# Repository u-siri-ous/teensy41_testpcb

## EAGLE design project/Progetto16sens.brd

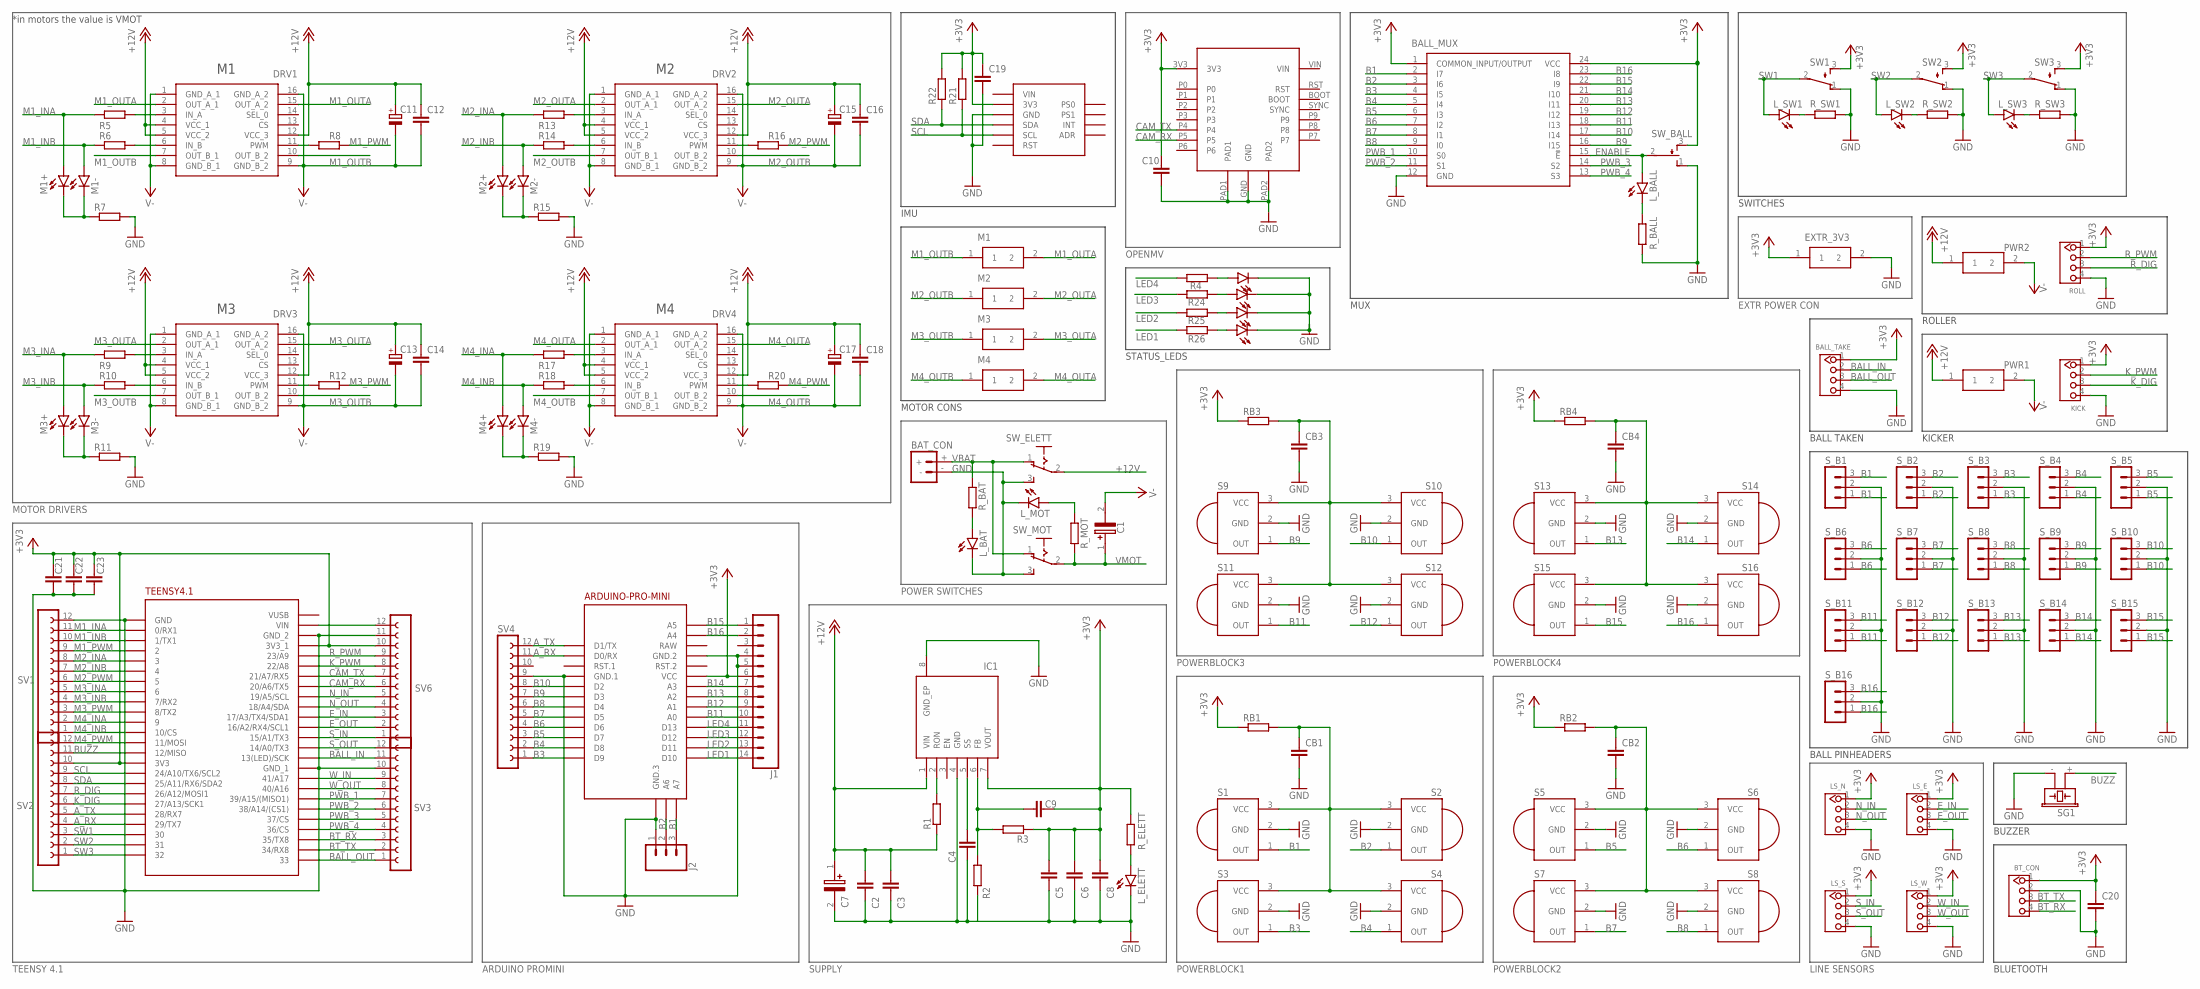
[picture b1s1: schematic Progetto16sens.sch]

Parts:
BALL_MUX: CD74HC4067M; SOIC127P1030X265-24N
BALL_TAKE: 4P-2.0; HW4-2.0
BAT_CON: BATTERY_CONN_DEANS; DEANS
BT_CON: 4P-2.0; HW4-2.0
C1, C7: EEV-FK1C152Q; FKV(H13)
C2, C3, C8: 100n; C0805
C4, C9: 22n; C0805
C5, C6, C10: 100u; C1206
C11, C13, C15, C17: CPOL-EUE; PANASONIC_E
C12, C14, C16, C18, C22, C23: C-EUC0805; C0805
C19, C20: 1u; C0805
C21: C-EUC1206; C1206
CB1, CB2, CB3, CB4: C-EUC0805; C0805
DRV1, DRV2, DRV3, DRV4: VNH7070ASTR; SOIC127P600X175-16N
EXTR_3V3: 43650-0201; 43650-0200
IC1: LMZ14202TZE-ADJ_NOPB; NDW0007A
J1: CONN_14; 1X14
J2: 455-1750-1-ND; 1X03
KICK: TWIG_2.0; 2.0_1X4
LED1, LED2, LED3, LED4: LEDCHIPLED_1206; CHIPLED_1206
LS_E: 4P-2.0; HW4-2.0
LS_N: 4P-2.0; HW4-2.0
LS_S: 4P-2.0; HW4-2.0
LS_W: 4P-2.0; HW4-2.0
L_BALL: LEDCHIPLED_1206; CHIPLED_1206
L_BAT: LEDCHIPLED_1206; CHIPLED_1206
L_ELETT: LEDCHIPLED_1206; CHIPLED_1206
L_MOT: LEDCHIPLED_1206; CHIPLED_1206
L_SW1, L_SW2, L_SW3: LEDCHIPLED_1206; CHIPLED_1206
M1, M2, M3, M4: 43650-0201; 43650-0200
M1+, M1-, M2+, M2-, M3+, M3-, M4+, M4-: LEDCHIPLED_1206; CHIPLED_1206
M5: ARDUINO-PRO-MINI; ARDUINO-PRO-MINI#NP
PWR1, PWR2: 43650-0201; 43650-0200
R1: 61,9k; M0805
R2: 1,07k; M0805
R3: 3,32k; M0805
R4, R24, R25, R26: R-EU_R0805; R0805
R5, R6, R7, R8, R9, R10, R11, R12, R13, R14, R15, R16, R17, R18, R19, R20: R-EU_M0805; M0805
R21, R22: 10k; M0805
RB1, RB2, RB3, RB4: R-EU_M0805; M0805
ROLL: TWIG_2.0; 2.0_1X4
R_BALL: R-EU_M0805; M0805
R_BAT: R-EU_M0805; M0805
R_ELETT: R-EU_M0805; M0805
R_MOT: R-EU_M0805; M0805
R_SW1, R_SW2, R_SW3: R-EU_M0805; M0805
S1, S2, S3, S4, S5, S6, S7, S8, S9, S10, S11, S12, S13, S14, S15, S16: PNA460XM
SG1: F/CM12P
SV1, SV2, SV3, SV4, SV6: FE12-1; FE12
SW1, SW2, SW3: TL32PO; TL3XPO
SW_BALL: TL38PO; TL3XPO
SW_ELETT: 255SB
SW_MOT: 255SB
S_B1, S_B2, S_B3, S_B4, S_B5, S_B6, S_B7, S_B8, S_B9, S_B10, S_B11, S_B12, S_B13, S_B14, S_B15, S_B16: MA03-1
U$1: TEENSY41_EDIT
U$2: OPENMV_H7
U$3: BNO055_BNO055

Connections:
+3V3: BALL_MUX.1 (COMMON_INPUT/OUTPUT), BALL_MUX.24 (VCC), BALL_TAKE.1, BT_CON.1, C5.1, C6.1, C8.1, C9.2, C10.1, C19.1, C20.1, C21.1, C22.1, C23.1, EXTR_3V3.1, IC1.7 (VOUT), J1.6, KICK.1, LS_E.1, LS_N.1, LS_S.1, LS_W.1, M5.J6.4 (VCC), R3.1, R21.2, R22.2, RB1.1, RB2.1, RB3.1, RB4.1, ROLL.1, R_ELETT.2, SV2.10, SV6.10, SW1.3 (S), SW2.3 (S), SW3.3 (S), SW_BALL.3 (S), U$1.3V3, U$1.3V3_1, U$2.3V3, U$3.3V3
+12V: C2.1, C3.1, C7.1 (+), IC1.1 (VIN), R1.1, SW_ELETT.2
A_RX: M5.J7.11 (D0/RX), SV2.4, SV4.11, U$1.29/TX7
A_TX: M5.J7.12 (D1/TX), SV2.5, SV4.12, U$1.28/RX7
B1: BALL_MUX.2 (I7), J2.3, M5.J3.3 (A7), S1.1 (OUT), S_B1.1, S_B1.3
B2: BALL_MUX.3 (I6), J2.2, M5.J3.2 (A6), S2.1 (OUT), S_B2.1, S_B2.3
B3: BALL_MUX.4 (I5), M5.J7.1 (D9), S3.1 (OUT), SV4.1, S_B3.1, S_B3.3
B4: BALL_MUX.5 (I4), M5.J7.2 (D8), S4.1 (OUT), SV4.2, S_B4.1, S_B4.3
B5: BALL_MUX.6 (I3), M5.J7.3 (D7), S5.1 (OUT), SV4.3, S_B5.1, S_B5.3
B6: BALL_MUX.7 (I2), M5.J7.4 (D6), S6.1 (OUT), SV4.4, S_B6.1, S_B6.3
B7: BALL_MUX.8 (I1), M5.J7.5 (D5), S7.1 (OUT), SV4.5, S_B7.1, S_B7.3
B8: BALL_MUX.9 (I0), M5.J7.6 (D4), S8.1 (OUT), SV4.6, S_B8.1, S_B8.3
B9: BALL_MUX.16 (I15), M5.J7.7 (D3), S9.1 (OUT), SV4.7, S_B9.1, S_B9.3
B10: BALL_MUX.17 (I14), M5.J7.8 (D2), S10.1 (OUT), SV4.8, S_B10.1, S_B10.3
B11: BALL_MUX.18 (I13), J1.10, M5.J6.8 (A0), S11.1 (OUT), S_B11.1, S_B11.3
B12: BALL_MUX.19 (I12), J1.9, M5.J6.7 (A1), S12.1 (OUT), S_B12.1, S_B12.3
B13: BALL_MUX.20 (I11), J1.8, M5.J6.6 (A2), S13.1 (OUT), S_B13.1, S_B13.3
B14: BALL_MUX.21 (I10), J1.7, M5.J6.5 (A3), S14.1 (OUT), S_B14.1, S_B14.3
B15: BALL_MUX.22 (I9), J1.1, M5.J2.2 (A5), S15.1 (OUT), S_B15.1, S_B15.3
B16: BALL_MUX.23 (I8), J1.2, M5.J2.1 (A4), S16.1 (OUT), S_B16.1, S_B16.3
BALL_IN: BALL_TAKE.2, SV3.11, U$1.13(LED)/SCK
BALL_OUT: BALL_TAKE.3, SV3.1, U$1.33
BT_RX: BT_CON.4, SV3.3, U$1.35/TX8
BT_TX: BT_CON.3, SV3.2, U$1.34/RX8
BUZZ: SG1.+ (1), SV2.11, U$1.12/MISO
CAM_RX: SV6.6, U$1.20/A6/TX5, U$2.P5
CAM_TX: SV6.7, U$1.21/A7/RX5, U$2.P4
ENABLE: BALL_MUX.15 (!E), L_BALL.A, SW_BALL.2
E_IN: LS_E.2, SV6.3, U$1.17/A3/TX4/SDA1
E_OUT: LS_E.3, SV6.2, U$1.16/A2/RX4/SCL1
GND: BALL_MUX.12 (GND), BALL_TAKE.4, BAT_CON.-, BT_CON.2, C2.2, C3.2, C4.2, C5.2, C6.2, C7.2 (-), C8.2, C10.2, C19.2, C20.2, C21.2, C22.2, C23.2, CB1.2, CB2.2, CB3.2, CB4.2, EXTR_3V3.2, IC1.4 (GND), IC1.8 (GND_EP), J1.4, J1.5, J2.1, KICK.4, LED1.C, LED2.C, LED3.C, LED4.C, LS_E.4, LS_N.4, LS_S.4, LS_W.4, L_BAT.C, L_ELETT.C, L_MOT.C, M5.J3.1 (GND.3), M5.J6.2 (GND.2), M5.J7.9 (GND.1), R2.1, R7.2, R11.2, R15.2, R19.2, ROLL.4, R_BALL.1, R_SW1.1, R_SW2.1, R_SW3.1, S1.2 (GND), S2.2 (GND), S3.2 (GND), S4.2 (GND), S5.2 (GND), S6.2 (GND), S7.2 (GND), S8.2 (GND), S9.2 (GND), S10.2 (GND), S11.2 (GND), S12.2 (GND), S13.2 (GND), S14.2 (GND), S15.2 (GND), S16.2 (GND), SG1.- (2), SV1.12, SV3.10, SV4.9, SV6.11, SW1.1 (O), SW2.1 (O), SW3.1 (O), SW_BALL.1 (O), SW_ELETT.3 (S), SW_MOT.3 (S), S_B1.2, S_B2.2, S_B3.2, S_B4.2, S_B5.2, S_B6.2, S_B7.2, S_B8.2, S_B9.2, S_B10.2, S_B11.2, S_B12.2, S_B13.2, S_B14.2, S_B15.2, S_B16.2, U$1.GND, U$1.GND_1, U$1.GND_2, U$2.GND, U$2.PAD1, U$2.PAD2, U$3.GND
K_DIG: KICK.3, SV2.6, U$1.27/A13/SCK1
K_PWM: KICK.2, SV6.8, U$1.22/A8
LED1: J1.14, M5.J6.12 (D10), R26.1
LED2: J1.13, M5.J6.11 (D11), R25.1
LED3: J1.12, M5.J6.10 (D12), R24.1
LED4: J1.11, M5.J6.9 (D13), R4.1
M1_INA: M1+.A, R5.1, SV1.11, U$1.0/RX1
M1_INB: M1-.A, R6.1, SV1.10, U$1.1/TX1
M1_OUTA: DRV1.2 (OUT_A_1), DRV1.15 (OUT_A_2), M1.2
M1_OUTB: DRV1.7 (OUT_B_1), DRV1.10 (OUT_B_2), M1.1
M1_PWM: R8.2, SV1.9, U$1.2
M2_INA: M2+.A, R13.1, SV1.8, U$1.3
M2_INB: M2-.A, R14.1, SV1.7, U$1.4
M2_OUTA: DRV2.2 (OUT_A_1), DRV2.15 (OUT_A_2), M2.2
M2_OUTB: DRV2.7 (OUT_B_1), DRV2.10 (OUT_B_2), M2.1
M2_PWM: R16.2, SV1.6, U$1.5
M3_INA: M3+.A, R9.1, SV1.5, U$1.6
M3_INB: M3-.A, R10.1, SV1.4, U$1.7/RX2
M3_OUTA: DRV3.2 (OUT_A_1), DRV3.15 (OUT_A_2), M3.2
M3_OUTB: DRV3.7 (OUT_B_1), DRV3.10 (OUT_B_2), M3.1
M3_PWM: R12.2, SV1.3, U$1.8/TX2
M4_INA: M4+.A, R17.1, SV1.2, U$1.9
M4_INB: M4-.A, R18.1, SV1.1, U$1.10/CS
M4_OUTA: DRV4.2 (OUT_A_1), DRV4.15 (OUT_A_2), M4.2
M4_OUTB: DRV4.7 (OUT_B_1), DRV4.10 (OUT_B_2), M4.1
M4_PWM: R20.2, SV2.12, U$1.11/MOSI
unnamed: L_SW2.C, R_SW2.2
unnamed: L_SW1.C, R_SW1.2
unnamed: L_SW3.C, R_SW3.2
unnamed: LED4.A, R4.2
unnamed: C4.1, IC1.5 (SS)
unnamed: L_BAT.A, R_BAT.2
unnamed: L_BALL.C, R_BALL.2
unnamed: L_MOT.A, R_MOT.1
unnamed: C9.1, IC1.6 (FB), R2.2, R3.2
unnamed: IC1.2 (RON), R1.2
unnamed: L_ELETT.A, R_ELETT.1
unnamed: LED2.A, R25.2
unnamed: LED3.A, R24.2
unnamed: LED1.A, R26.2
unnamed: M1+.C, M1-.C, R7.1
unnamed: DRV1.3 (IN_A), R5.2
unnamed: DRV1.6 (IN_B), R6.2
unnamed: DRV1.11 (PWM), R8.1
unnamed: DRV3.3 (IN_A), R9.2
unnamed: DRV3.6 (IN_B), R10.2
unnamed: M3+.C, M3-.C, R11.1
unnamed: DRV3.11 (PWM), R12.1
unnamed: DRV2.3 (IN_A), R13.2
unnamed: DRV2.6 (IN_B), R14.2
unnamed: M2+.C, M2-.C, R15.1
unnamed: DRV2.11 (PWM), R16.1
unnamed: DRV4.3 (IN_A), R17.2
unnamed: DRV4.6 (IN_B), R18.2
unnamed: M4+.C, M4-.C, R19.1
unnamed: DRV4.11 (PWM), R20.1
unnamed: SV6.12, U$1.VIN
N_IN: LS_N.2, SV6.5, U$1.19/A5/SCL
N_OUT: LS_N.3, SV6.4, U$1.18/A4/SDA
PWB_1: BALL_MUX.10 (S0), SV3.7, U$1.39/A15/(MISO1)
PWB_2: BALL_MUX.11 (S1), SV3.6, U$1.38/A14/(CS1)
PWB_3: BALL_MUX.14 (S2), SV3.5, U$1.37/CS
PWB_4: BALL_MUX.13 (S3), SV3.4, U$1.36/CS
PWR_B1: CB1.1, RB1.2, S1.3 (VCC), S2.3 (VCC), S3.3 (VCC), S4.3 (VCC)
PWR_B2: CB2.1, RB2.2, S5.3 (VCC), S6.3 (VCC), S7.3 (VCC), S8.3 (VCC)
PWR_B3: CB3.1, RB3.2, S9.3 (VCC), S10.3 (VCC), S11.3 (VCC), S12.3 (VCC)
PWR_B4: CB4.1, RB4.2, S13.3 (VCC), S14.3 (VCC), S15.3 (VCC), S16.3 (VCC)
RAW: M5.J6.1 (RAW)
R_DIG: ROLL.3, SV2.7, U$1.26/A12/MOSI1
R_PWM: ROLL.2, SV6.9, U$1.23/A9
SCL: R21.1, SV2.9, U$1.24/A10/TX6/SCL2, U$3.SCL
SDA: R22.1, SV2.8, U$1.25/A11/RX6/SDA2, U$3.SDA
SW1: L_SW1.A, SV2.3, SW1.2, U$1.30
SW2: L_SW2.A, SV2.2, SW2.2, U$1.31
SW3: L_SW3.A, SV2.1, SW3.2, U$1.32
S_IN: LS_S.2, SV6.1, U$1.15/A1/RX3 (15/A1/TX3)
S_OUT: LS_S.3, SV3.12, U$1.14/A0/TX3
V-: C1.2 (-), C11.-, C12.2, C13.-, C14.2, C15.-, C16.2, C17.-, C18.2, DRV1.1 (GND_A_1), DRV1.8 (GND_B_1), DRV1.9 (GND_B_2), DRV1.16 (GND_A_2), DRV2.1 (GND_A_1), DRV2.8 (GND_B_1), DRV2.9 (GND_B_2), DRV2.16 (GND_A_2), DRV3.1 (GND_A_1), DRV3.8 (GND_B_1), DRV3.9 (GND_B_2), DRV3.16 (GND_A_2), DRV4.1 (GND_A_1), DRV4.8 (GND_B_1), DRV4.9 (GND_B_2), DRV4.16 (GND_A_2), PWR1.2, PWR2.2
VBAT: BAT_CON.+, R_BAT.1, SW_ELETT.1 (O), SW_MOT.1 (O)
VMOT: C1.1 (+), C11.+, C12.1, C13.+, C14.1, C15.+, C16.1, C17.+, C18.1, DRV1.4 (VCC_1), DRV1.5 (VCC_2), DRV1.12 (VCC_3), DRV2.4 (VCC_1), DRV2.5 (VCC_2), DRV2.12 (VCC_3), DRV3.4 (VCC_1), DRV3.5 (VCC_2), DRV3.12 (VCC_3), DRV4.4 (VCC_1), DRV4.5 (VCC_2), DRV4.12 (VCC_3), PWR1.1, PWR2.1, R_MOT.2, SW_MOT.2
W_IN: LS_W.2, SV3.9, U$1.41/A17
W_OUT: LS_W.3, SV3.8, U$1.40/A16

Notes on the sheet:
TEENSY 4.1
ARDUINO PROMINI
POWERBLOCK1
POWERBLOCK2
POWERBLOCK3
POWERBLOCK4
SUPPLY
MOTOR DRIVERS
EXTR POWER CON
LINE SENSORS
OPENMV
POWER SWITCHES
MOTOR CONS
IMU
BLUETOOTH
BALL PINHEADERS
MUX
TEENSY4.1
BUZZER
SWITCHES
STATUS_LEDS
ROLLER
KICKER
*in motors the value is VMOT
BALL TAKEN

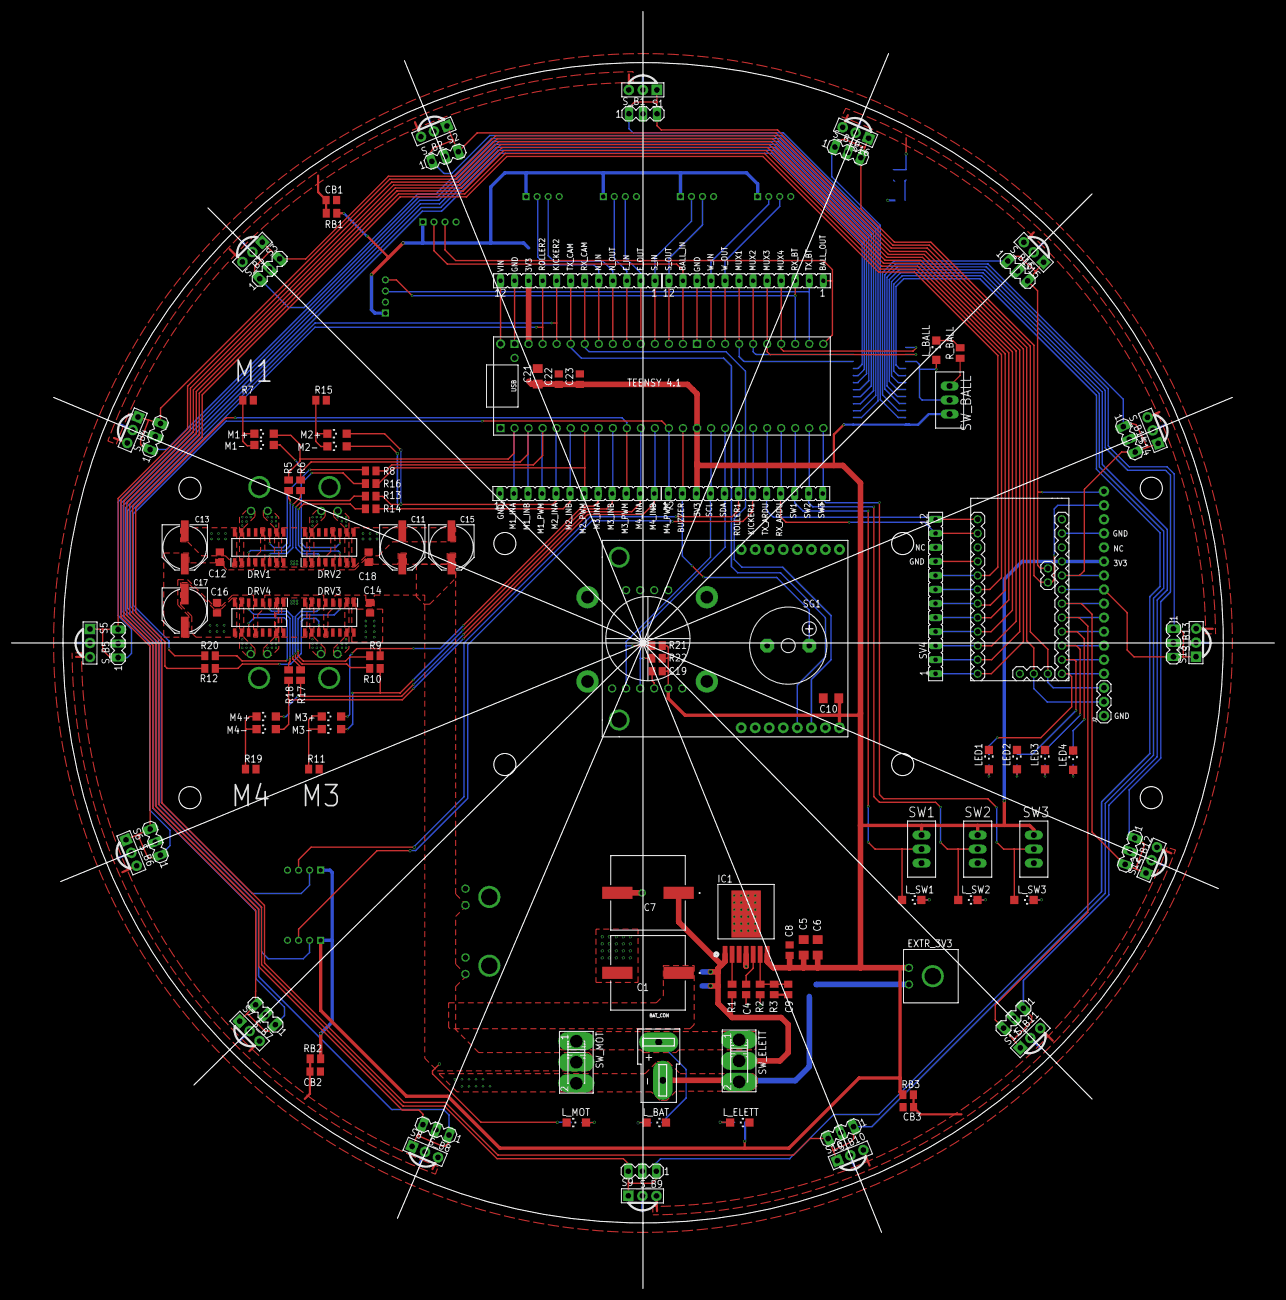
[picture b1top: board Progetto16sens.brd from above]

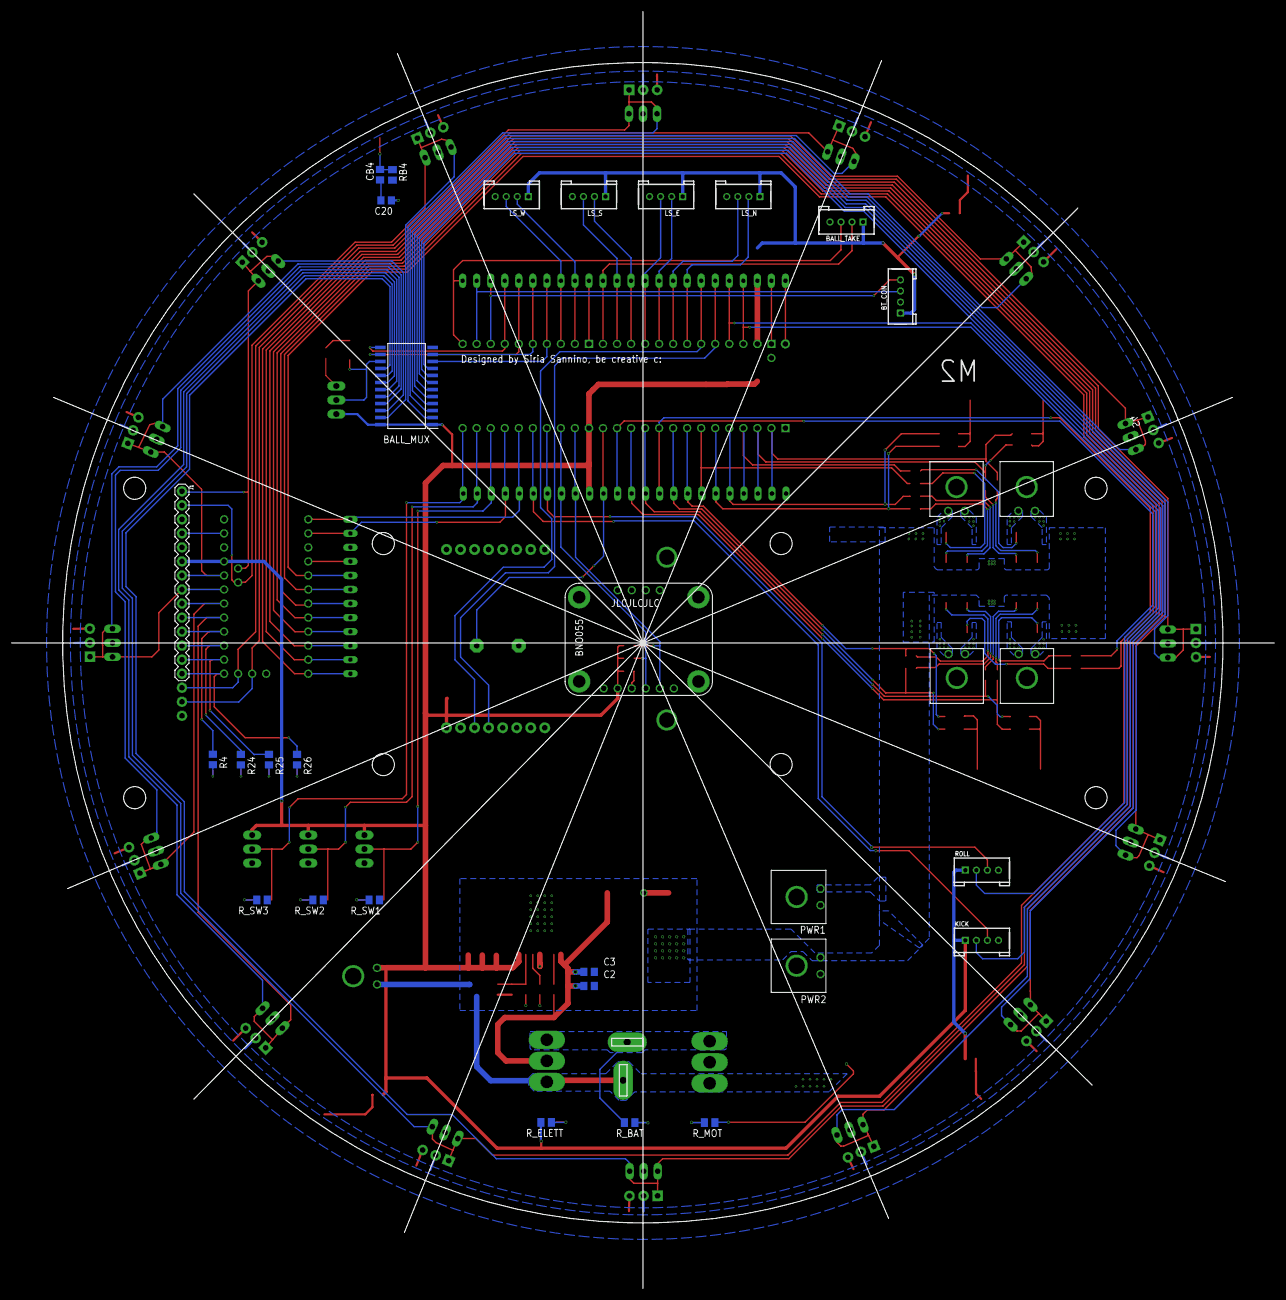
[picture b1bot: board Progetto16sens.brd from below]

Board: 2 copper layers, 210.0 x 210.0 mm, 154 parts (32 on the bottom side), 112 nets.

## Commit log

2021-03-23 first commit, yay! c:
2021-03-23 added camera and motor cons
2021-03-24 integrated new libs, added a todo and line sensors
2021-03-24 added motor drivers, found a problem in brd creation tho :c
2021-03-27 created the array of ball sensors, now to understand how to rotate them right, implementing a custom made IMU lbr
2021-03-27 started placing components for optimal wiring
2021-03-27 added IMU and BT
2021-03-28 added ball switches, what now?
2021-03-28 rotated ball sensors, what now?
2021-03-28 rearranged schematic
2021-04-08 mh, kinda dunno what to do
2021-04-08 mh, kinda dunno what to do part. 2
2021-04-09 mh, kinda dunno what to do part. 3, but added supply and arranged things
2021-04-24 part 3
2021-04-27 a lot of things addedgit add .
2021-04-27 new ball sens' layout
2021-04-27 felt like it todaygit add . the aesthetic is coming in, but i dont know how to do things help
2021-04-29 added cons, starting wiring (hopefully)
2021-04-29 edited libraries, to edit even further
2021-04-29 maybe started the doc, in italian idk why
2021-05-02 help
2021-05-03 started wiring
2021-05-04 started wiring for realllllll
2021-05-04 started wiring for realllllll 2
2021-05-06 greve
2021-05-06 im tired
2021-05-11 aaaaaaaaaaaaaaaaa
2021-05-11 aaaaaaaaaaaaaaaaaaaaaaaaaaaaa
2021-05-16 elaborato
2021-05-16 elaborato pt.2
2021-05-17 elaborato checking in three days
2021-05-18 elaborato checking in two days
2021-05-18 aaaaaaaaaaaaaaaaaaaaa
2021-05-18 first autorouter test....could have gone better
2021-05-19 elaborato almost done, trying to turn a draft it tomorrow afternoon
2021-05-20 turned in elaborato
2021-05-21 turned in elaborato, continuing brd
2021-05-22 continuing brd
2021-05-25 elab n 2
2021-05-25 elab n 3, sending draft 2 tomorrow
2021-05-26 halfway done with wiring SEE WIRESTUB ERROR
2021-05-30 elaborato almost done, board needs some fixing
2021-05-30 BOARD IS DONE EVEN IF IT HAS SOME ZOZZATE and some drill size drc errors but what can u do nowadays
2021-05-30 okay, reread elaborato today is the dayyy
2021-06-09 getting ready

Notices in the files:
parts and their libraries:
SparkFun-Connectors: Licensing: Creative Commons ShareAlike 4.0 International - https://creativecommons.org/licenses/by-sa/4.0
arduinopromininew: Released under the Creative Commons Attribution 4.0 International License: http://creativecommons.org/licenses/by/4.0
